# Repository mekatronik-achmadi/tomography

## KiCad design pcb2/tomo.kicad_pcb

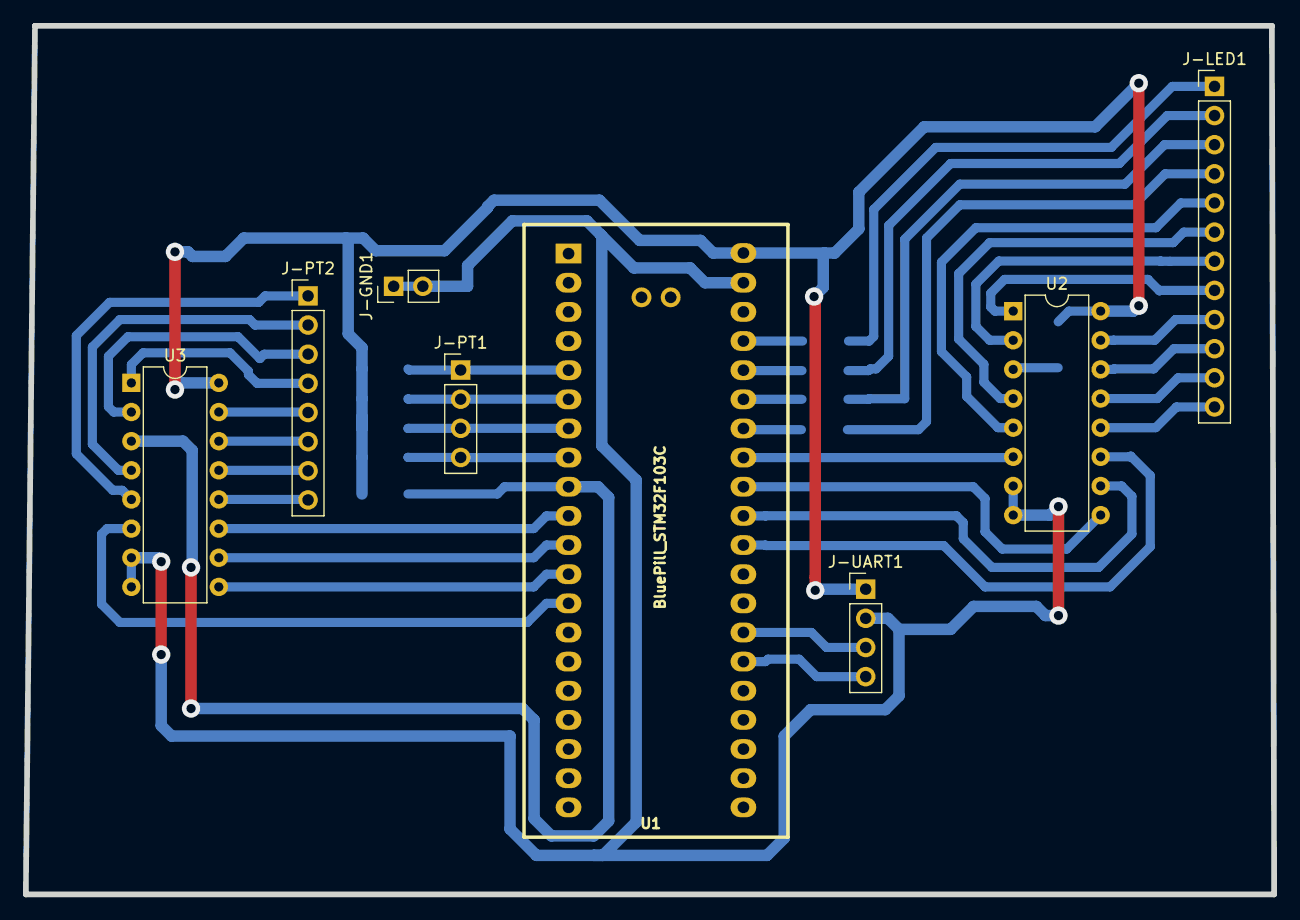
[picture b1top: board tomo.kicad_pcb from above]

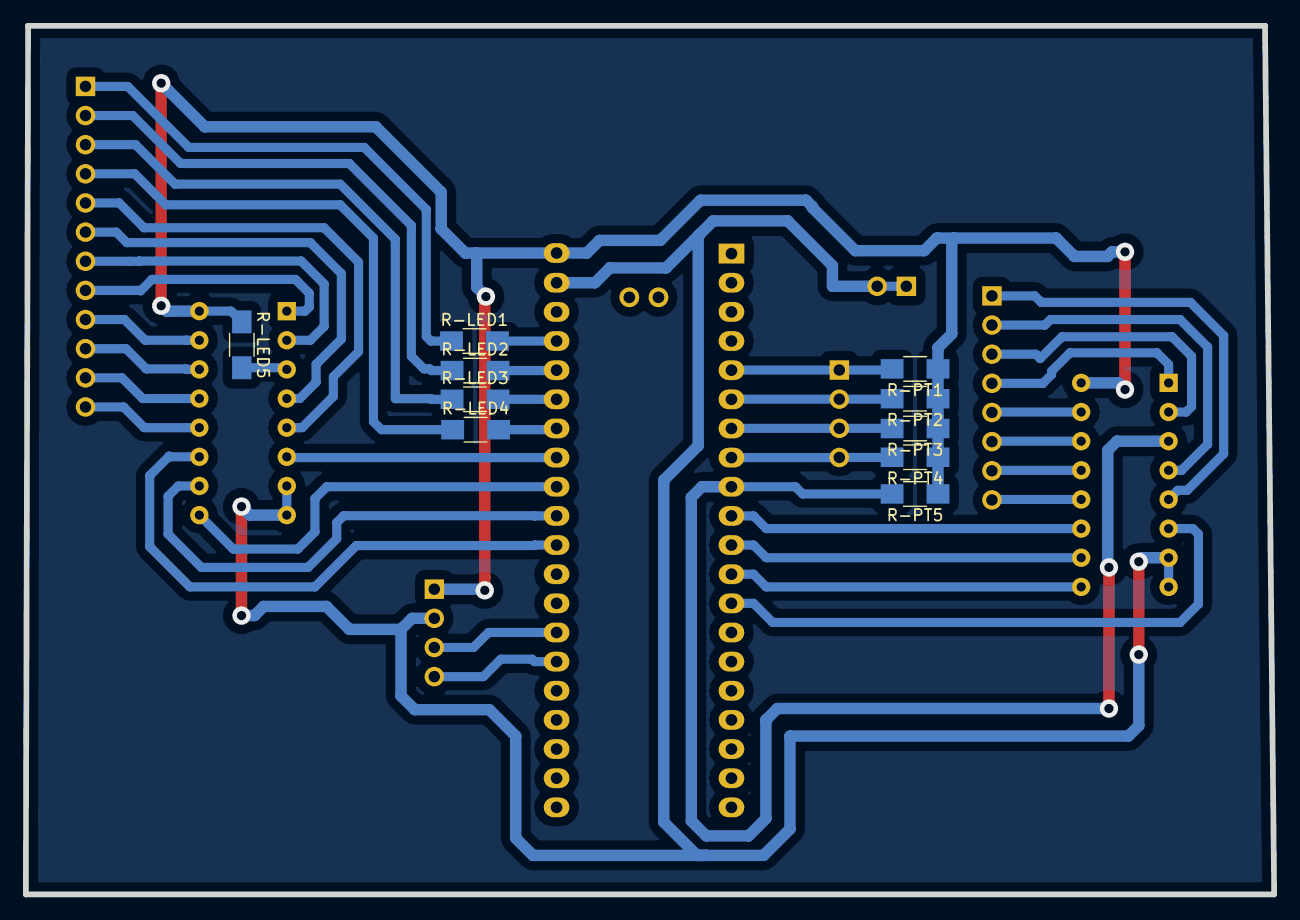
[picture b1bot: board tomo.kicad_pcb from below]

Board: 2 copper layers, 108.8 x 75.7 mm, 18 parts (10 on the bottom side), 42 nets.

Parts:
J-GND1: CONN_01X02; Pin_Header_Straight_1x02_Pitch2.54mm
J-LED1: CONN_01X12; Pin_Header_Straight_1x12_Pitch2.54mm
J-PT1: CONN_01X04; Pin_Header_Straight_1x04_Pitch2.54mm
J-PT2: CONN_01X08; Pin_Header_Straight_1x08_Pitch2.54mm
J-UART1: CONN_01X04; Pin_Header_Straight_1x04_Pitch2.54mm
R-LED1, R-LED2, R-LED3, R-LED4, R-LED5: 100; R_1206_HandSoldering
R-PT1, R-PT2, R-PT3, R-PT4, R-PT5: 100K; R_1206_HandSoldering
U1: BluePill_STM32F103C
U2, U3: 4051; DIP-16_W7.62mm

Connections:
/L0: J-LED1.1, R-LED1.1
/L1: J-LED1.2, R-LED2.1
/L2: J-LED1.3, R-LED3.1
/L3: J-LED1.4, R-LED4.1
/L4: J-LED1.5, U2.5
/L5: J-LED1.6, U2.4
/L6: J-LED1.7, U2.2
/L7: J-LED1.8, U2.1
/L8: J-LED1.9, U2.15
/L9: J-LED1.10, U2.14
/L10: J-LED1.11, U2.13
/L11: J-LED1.12, U2.12
/L_A: U1.30, U2.11
/L_B: U1.31, U2.10
/L_C: U1.32, U2.9
/L_INH: U1.33, U2.6
/P0: J-PT1.1, R-PT1.2, U1.5
/P1: J-PT1.2, R-PT2.2, U1.6
/P2: J-PT1.3, R-PT3.2, U1.7
/P3: J-PT1.4, R-PT4.2, U1.8
/P4: J-PT2.1, U3.5
/P5: J-PT2.2, U3.4
/P6: J-PT2.3, U3.2
/P7: J-PT2.4, U3.1
/P8: J-PT2.5, U3.15
/P9: J-PT2.6, U3.14
/P10: J-PT2.7, U3.13
/P11: J-PT2.8, U3.12
/P_A: U1.10, U3.11
/P_ADC: R-PT5.2, U1.9, U3.3
/P_B: U1.11, U3.10
/P_C: U1.12, U3.9
/P_INH: U1.13, U3.6
/RX: J-UART1.3, U1.27
/TX: J-UART1.4, U1.26
unnamed: R-LED1.2, U1.37
unnamed: R-LED2.2, U1.36
unnamed: R-LED3.2, U1.35
unnamed: R-LED4.2, U1.34
unnamed: R-LED5.2, U2.3
VDD: J-UART1.1, R-LED5.1, R-PT1.1, R-PT2.1, R-PT3.1, R-PT4.1, R-PT5.1, U1.40, U2.16, U3.16
VSS: J-GND1.1, J-GND1.2, J-UART1.2, U1.39, U2.7, U2.8, U3.7, U3.8

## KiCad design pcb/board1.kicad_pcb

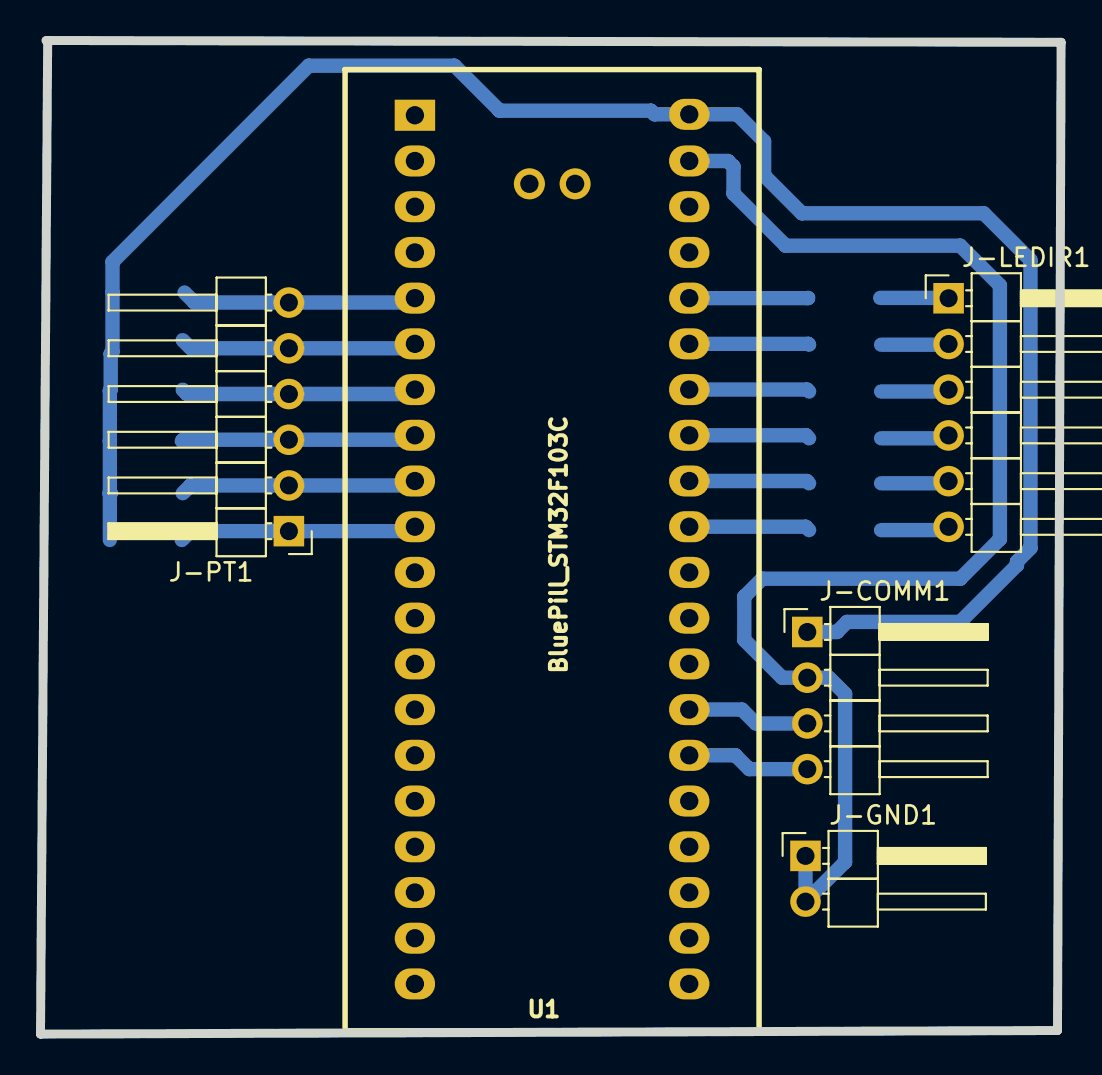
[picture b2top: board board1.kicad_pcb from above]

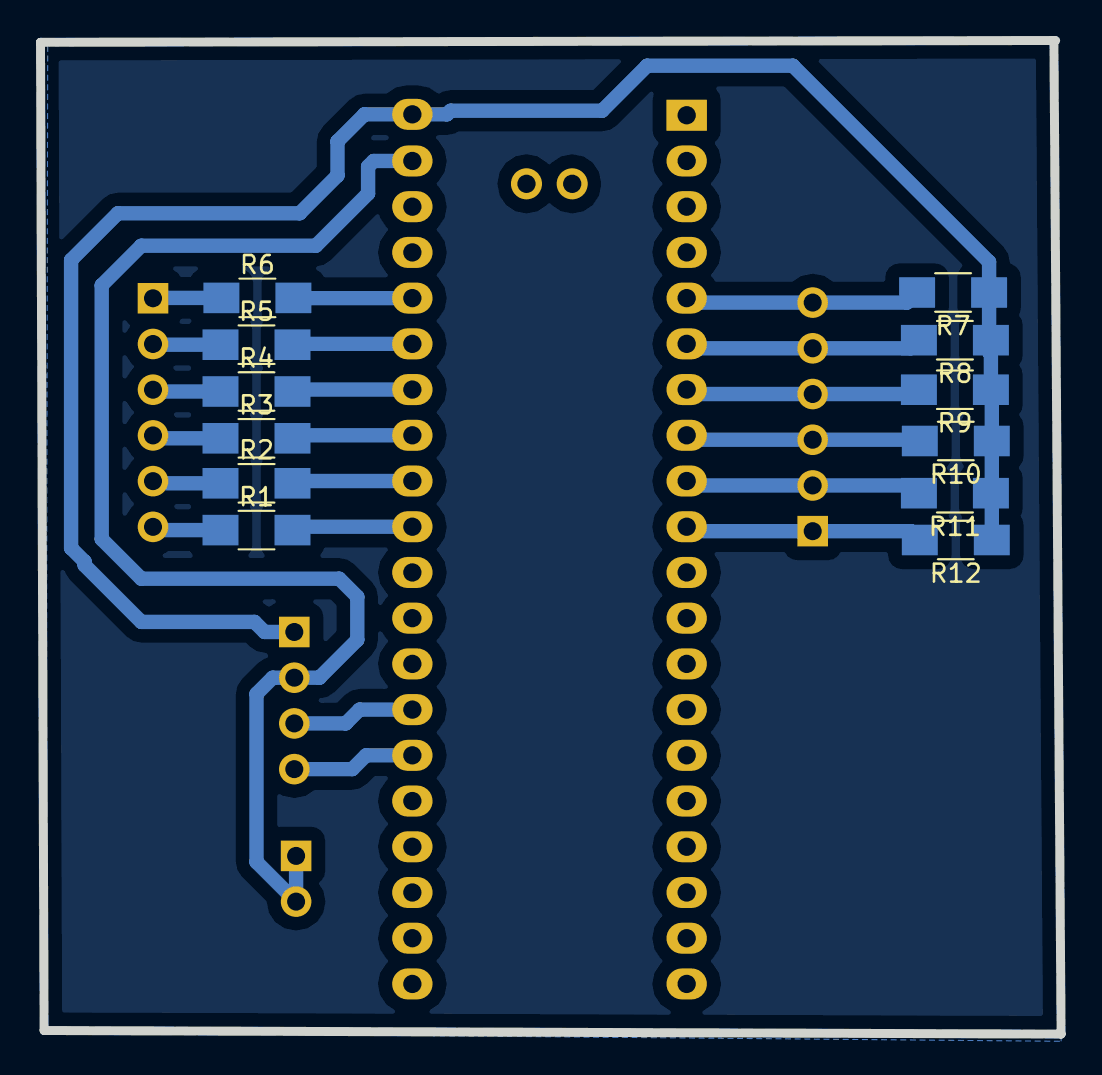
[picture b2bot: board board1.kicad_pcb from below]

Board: 2 copper layers, 56.7 x 55.2 mm, 17 parts (12 on the bottom side), 22 nets.

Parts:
J-COMM1: CONN_01X04; Pin_Header_Angled_1x04_Pitch2.54mm
J-GND1: CONN_01X02; Pin_Header_Angled_1x02_Pitch2.54mm
J-LEDIR1: CONN_01X06; Pin_Header_Angled_1x06_Pitch2.54mm
J-PT1: CONN_01X06; Pin_Header_Angled_1x06_Pitch2.54mm
R1, R2, R3, R4, R5, R6: 100; R_1206_HandSoldering
R7, R8, R9, R10, R11, R12: 220k; R_1206_HandSoldering
U1: BluePill_STM32F103C

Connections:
+3V3: J-COMM1.1, R7.1, R8.1, R9.1, R10.1, R11.1, R12.1, U1.40
/LD1: R1.2, U1.31
/LD2: R2.2, U1.32
/LD3: R3.2, U1.33
/LD4: R4.2, U1.34
/LD5: R5.2, U1.35
/LD6: R6.2, U1.36
/PT1: J-PT1.6, R7.2, U1.5
/PT2: J-PT1.5, R8.2, U1.6
/PT3: J-PT1.4, R9.2, U1.7
/PT4: J-PT1.3, R10.2, U1.8
/PT5: J-PT1.2, R11.2, U1.9
/PT6: J-PT1.1, R12.2, U1.10
/RX: J-COMM1.3, U1.27
/TX: J-COMM1.4, U1.26
GND: J-COMM1.2, J-GND1.1, J-GND1.2, U1.39
unnamed: J-LEDIR1.1, R6.1
unnamed: J-LEDIR1.2, R5.1
unnamed: J-LEDIR1.3, R4.1
unnamed: J-LEDIR1.4, R3.1
unnamed: J-LEDIR1.5, R2.1
unnamed: J-LEDIR1.6, R1.1

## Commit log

2019-01-17 pcb 2
2019-01-21 tambahan obj
2019-02-04 expand to 12x12 step
2019-02-09 tes ok
